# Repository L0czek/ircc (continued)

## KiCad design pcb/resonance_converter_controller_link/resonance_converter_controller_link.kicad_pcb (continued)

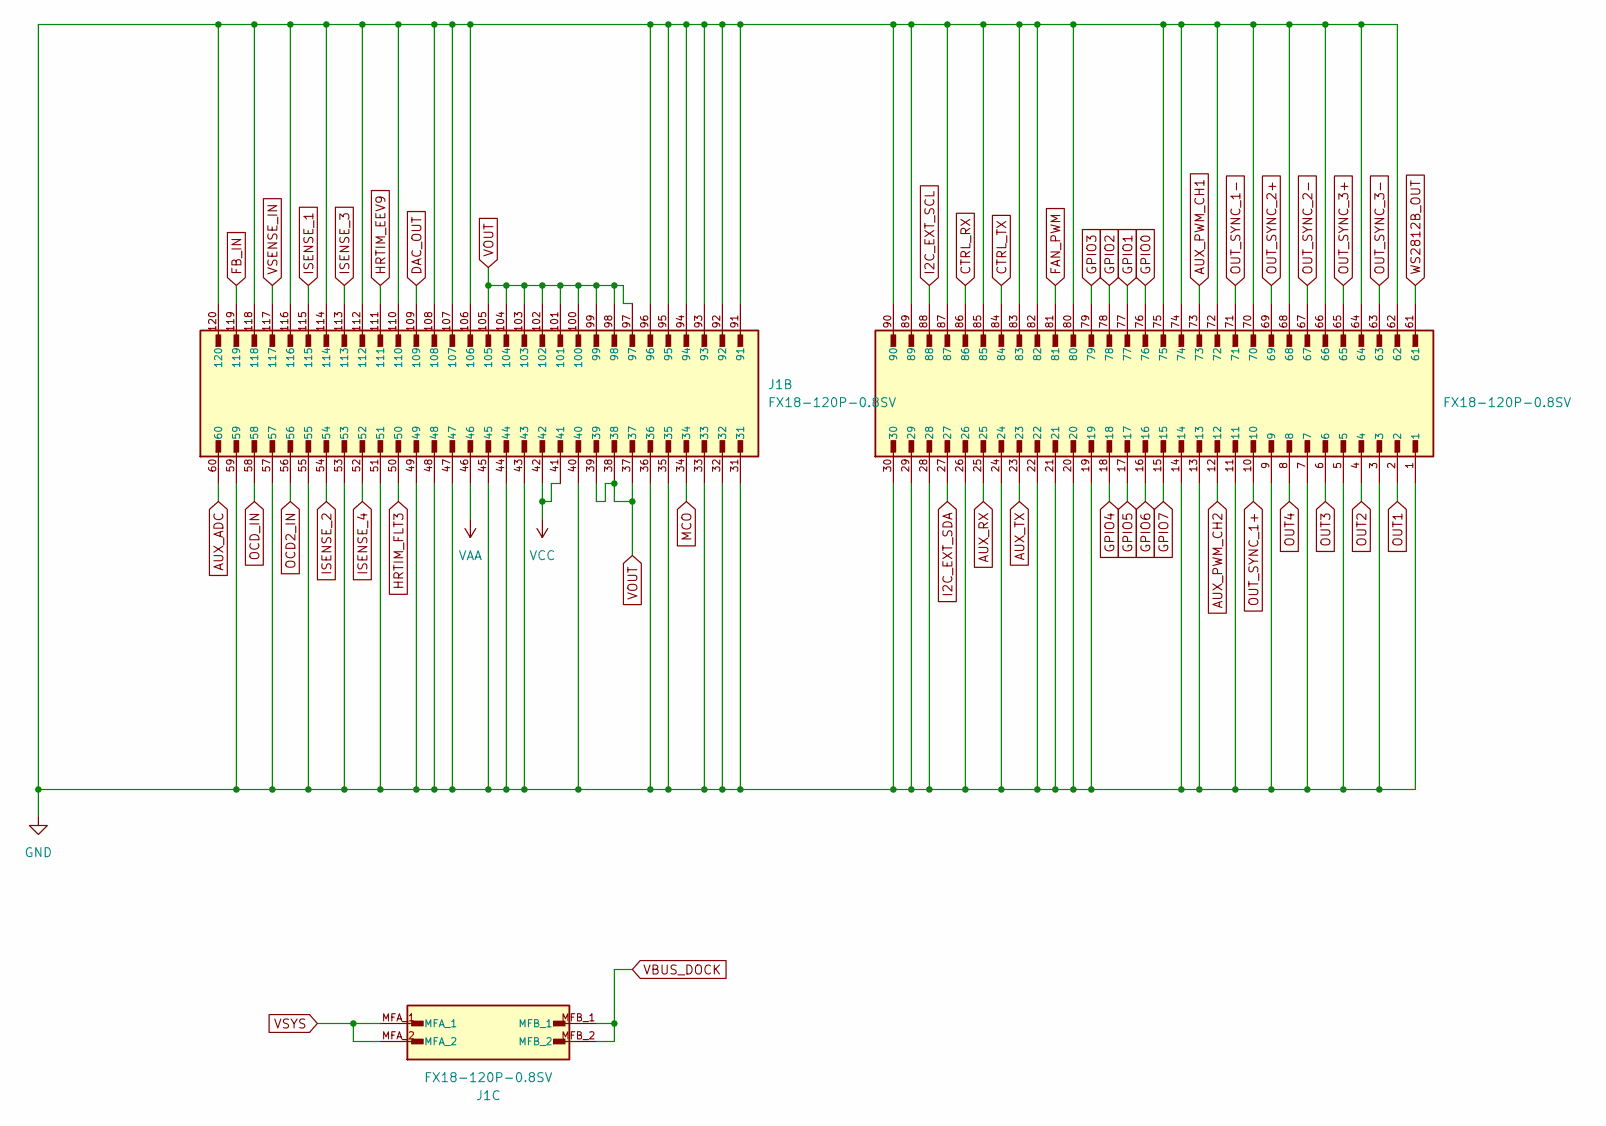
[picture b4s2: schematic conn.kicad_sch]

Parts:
J1: FX18-120P-0.8SV; HIROSE_FX18-120P-0.8SV; PARTREV 11.07.21

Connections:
AUX_ADC: J1.60; also elsewhere on the board
AUX_PWM_CH1: J1.73; also elsewhere on the board
AUX_PWM_CH2: J1.12; also elsewhere on the board
AUX_RX: J1.25; also elsewhere on the board
AUX_TX: J1.23; also elsewhere on the board
CTRL_RX: J1.86; also elsewhere on the board
CTRL_TX: J1.84; also elsewhere on the board
DAC_OUT: J1.109; also elsewhere on the board
FAN_PWM: J1.81; also elsewhere on the board
FB_IN: J1.119; also elsewhere on the board
GND: J1.1, J1.3, J1.5, J1.7, J1.9, J1.11, J1.13, J1.14, J1.19, J1.20, J1.21, J1.22, J1.24, J1.26, J1.28, J1.29, J1.30, J1.31, J1.32, J1.33, J1.35, J1.36, J1.40, J1.43, J1.44, J1.45, J1.47, J1.48, J1.49, J1.51, J1.53, J1.55, J1.57, J1.59, J1.62, J1.64, J1.66, J1.68, J1.70, J1.72, J1.74, J1.75, J1.80, J1.82, J1.83, J1.85, J1.87, J1.89, J1.90, J1.91, J1.92, J1.93, J1.94, J1.95, J1.96, J1.106, J1.107, J1.108, J1.110, J1.112, J1.114, J1.116, J1.118, J1.120; also elsewhere on the board
GPIO0: J1.76; also elsewhere on the board
GPIO1: J1.77; also elsewhere on the board
GPIO2: J1.78; also elsewhere on the board
GPIO3: J1.79; also elsewhere on the board
GPIO4: J1.18; also elsewhere on the board
GPIO5: J1.17; also elsewhere on the board
GPIO6: J1.16; also elsewhere on the board
GPIO7: J1.15; also elsewhere on the board
HRTIM_EEV9: J1.111; also elsewhere on the board
HRTIM_FLT3: J1.50; also elsewhere on the board
I2C_EXT_SCL: J1.88; also elsewhere on the board
I2C_EXT_SDA: J1.27; also elsewhere on the board
ISENSE_1: J1.115; also elsewhere on the board
ISENSE_2: J1.54; also elsewhere on the board
ISENSE_3: J1.113; also elsewhere on the board
ISENSE_4: J1.52; also elsewhere on the board
MCO: J1.34; also elsewhere on the board
OCD2_IN: J1.56; also elsewhere on the board
OCD_IN: J1.58; also elsewhere on the board
OUT1: J1.2; also elsewhere on the board
OUT2: J1.4; also elsewhere on the board
OUT3: J1.6; also elsewhere on the board
OUT4: J1.8; also elsewhere on the board
OUT_SYNC_1+: J1.10; also elsewhere on the board
OUT_SYNC_1-: J1.71; also elsewhere on the board
OUT_SYNC_2+: J1.69; also elsewhere on the board
OUT_SYNC_2-: J1.67; also elsewhere on the board
OUT_SYNC_3+: J1.65; also elsewhere on the board
OUT_SYNC_3-: J1.63; also elsewhere on the board
VAA: J1.46; also elsewhere on the board
VBUS_DOCK: J1.MFB_1, J1.MFB_2; also elsewhere on the board
VCC: J1.41, J1.42; also elsewhere on the board
VOUT: J1.37, J1.38, J1.39, J1.97, J1.98, J1.99, J1.100, J1.101, J1.102, J1.103, J1.104, J1.105; also elsewhere on the board
VSENSE_IN: J1.117; also elsewhere on the board
VSYS: J1.MFA_1, J1.MFA_2; also elsewhere on the board
WS2812B_OUT: J1.61; also elsewhere on the board

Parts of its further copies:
J2: FX18-120P-0.8SV; HIROSE_FX18-120P-0.8SV; PARTREV 11.07.21

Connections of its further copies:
AUX_ADC: J2.60; also elsewhere on the board
AUX_PWM_CH1: J2.73; also elsewhere on the board
AUX_PWM_CH2: J2.12; also elsewhere on the board
AUX_RX: J2.25; also elsewhere on the board
AUX_TX: J2.23; also elsewhere on the board
CTRL_RX: J2.86; also elsewhere on the board
CTRL_TX: J2.84; also elsewhere on the board
DAC_OUT: J2.109; also elsewhere on the board
FAN_PWM: J2.81; also elsewhere on the board
FB_IN: J2.119; also elsewhere on the board
GND: J2.1, J2.3, J2.5, J2.7, J2.9, J2.11, J2.13, J2.14, J2.19, J2.20, J2.21, J2.22, J2.24, J2.26, J2.28, J2.29, J2.30, J2.31, J2.32, J2.33, J2.35, J2.36, J2.40, J2.43, J2.44, J2.45, J2.47, J2.48, J2.49, J2.51, J2.53, J2.55, J2.57, J2.59, J2.62, J2.64, J2.66, J2.68, J2.70, J2.72, J2.74, J2.75, J2.80, J2.82, J2.83, J2.85, J2.87, J2.89, J2.90, J2.91, J2.92, J2.93, J2.94, J2.95, J2.96, J2.106, J2.107, J2.108, J2.110, J2.112, J2.114, J2.116, J2.118, J2.120; also elsewhere on the board
GPIO0: J2.76; also elsewhere on the board
GPIO1: J2.77; also elsewhere on the board
GPIO2: J2.78; also elsewhere on the board
GPIO3: J2.79; also elsewhere on the board
GPIO4: J2.18; also elsewhere on the board
GPIO5: J2.17; also elsewhere on the board
GPIO6: J2.16; also elsewhere on the board
GPIO7: J2.15; also elsewhere on the board
HRTIM_EEV9: J2.111; also elsewhere on the board
HRTIM_FLT3: J2.50; also elsewhere on the board
I2C_EXT_SCL: J2.88; also elsewhere on the board
I2C_EXT_SDA: J2.27; also elsewhere on the board
ISENSE_1: J2.115; also elsewhere on the board
ISENSE_2: J2.54; also elsewhere on the board
ISENSE_3: J2.113; also elsewhere on the board
ISENSE_4: J2.52; also elsewhere on the board
MCO: J2.34; also elsewhere on the board
OCD2_IN: J2.56; also elsewhere on the board
OCD_IN: J2.58; also elsewhere on the board
OUT1: J2.2; also elsewhere on the board
OUT2: J2.4; also elsewhere on the board
OUT3: J2.6; also elsewhere on the board
OUT4: J2.8; also elsewhere on the board
OUT_SYNC_1+: J2.10; also elsewhere on the board
OUT_SYNC_1-: J2.71; also elsewhere on the board
OUT_SYNC_2+: J2.69; also elsewhere on the board
OUT_SYNC_2-: J2.67; also elsewhere on the board
OUT_SYNC_3+: J2.65; also elsewhere on the board
OUT_SYNC_3-: J2.63; also elsewhere on the board
VAA: J2.46; also elsewhere on the board
VBUS_DOCK: J2.MFB_1, J2.MFB_2; also elsewhere on the board
VCC: J2.41, J2.42; also elsewhere on the board
VOUT: J2.37, J2.38, J2.39, J2.97, J2.98, J2.99, J2.100, J2.101, J2.102, J2.103, J2.104, J2.105; also elsewhere on the board
VSENSE_IN: J2.117; also elsewhere on the board
VSYS: J2.MFA_1, J2.MFA_2; also elsewhere on the board
WS2812B_OUT: J2.61; also elsewhere on the board

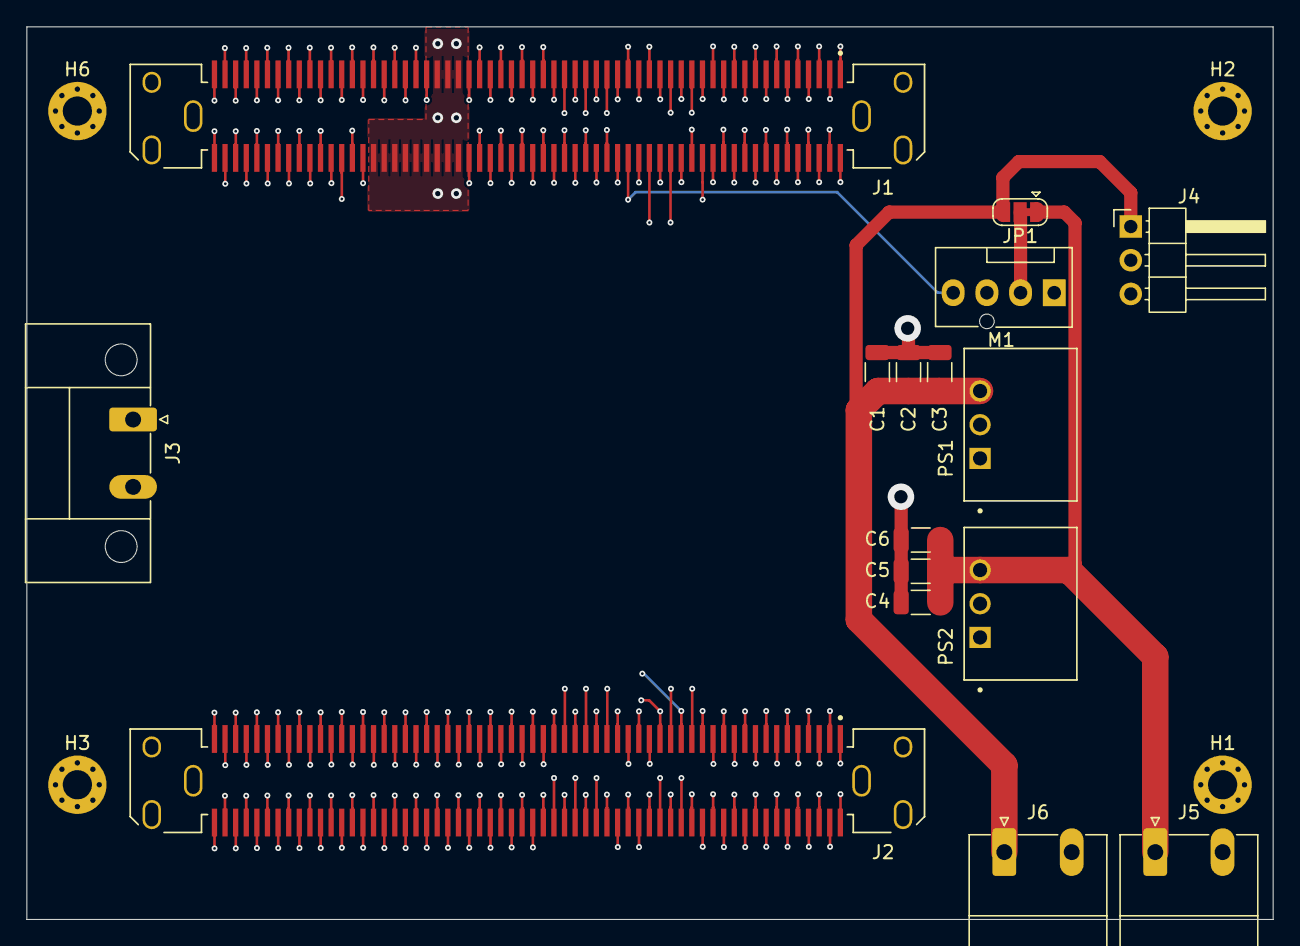
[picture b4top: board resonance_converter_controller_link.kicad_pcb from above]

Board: 6 copper layers, 94.0 x 67.3 mm, 20 parts (0 on the bottom side), 50 nets.

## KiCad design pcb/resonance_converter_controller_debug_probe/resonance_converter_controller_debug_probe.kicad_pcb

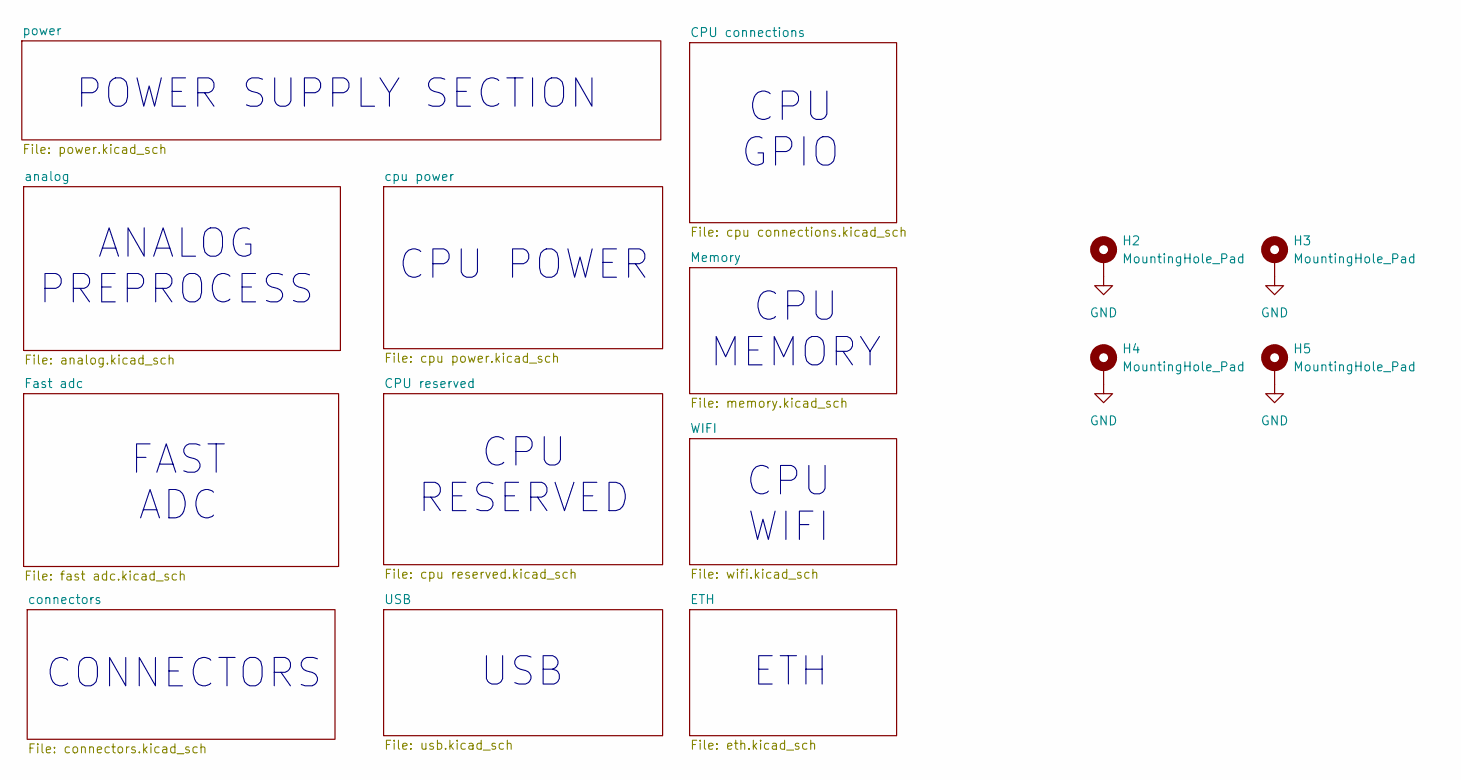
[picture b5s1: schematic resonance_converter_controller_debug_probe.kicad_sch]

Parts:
H2, H3, H4, H5: MountingHole_Pad; MountingHole_2.5mm_Pad_Via

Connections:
GND: H2.1 (1_1), H3.1 (1_1), H4.1 (1_1), H5.1 (1_1); also elsewhere on the board

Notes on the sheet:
CONNECTORS
CPU RESERVED
CPU GPIO
FAST ADC
ANALOG PREPROCESS
CPU MEMORY
USB
ETH
CPU POWER
CPU WIFI
POWER SUPPLY SECTION

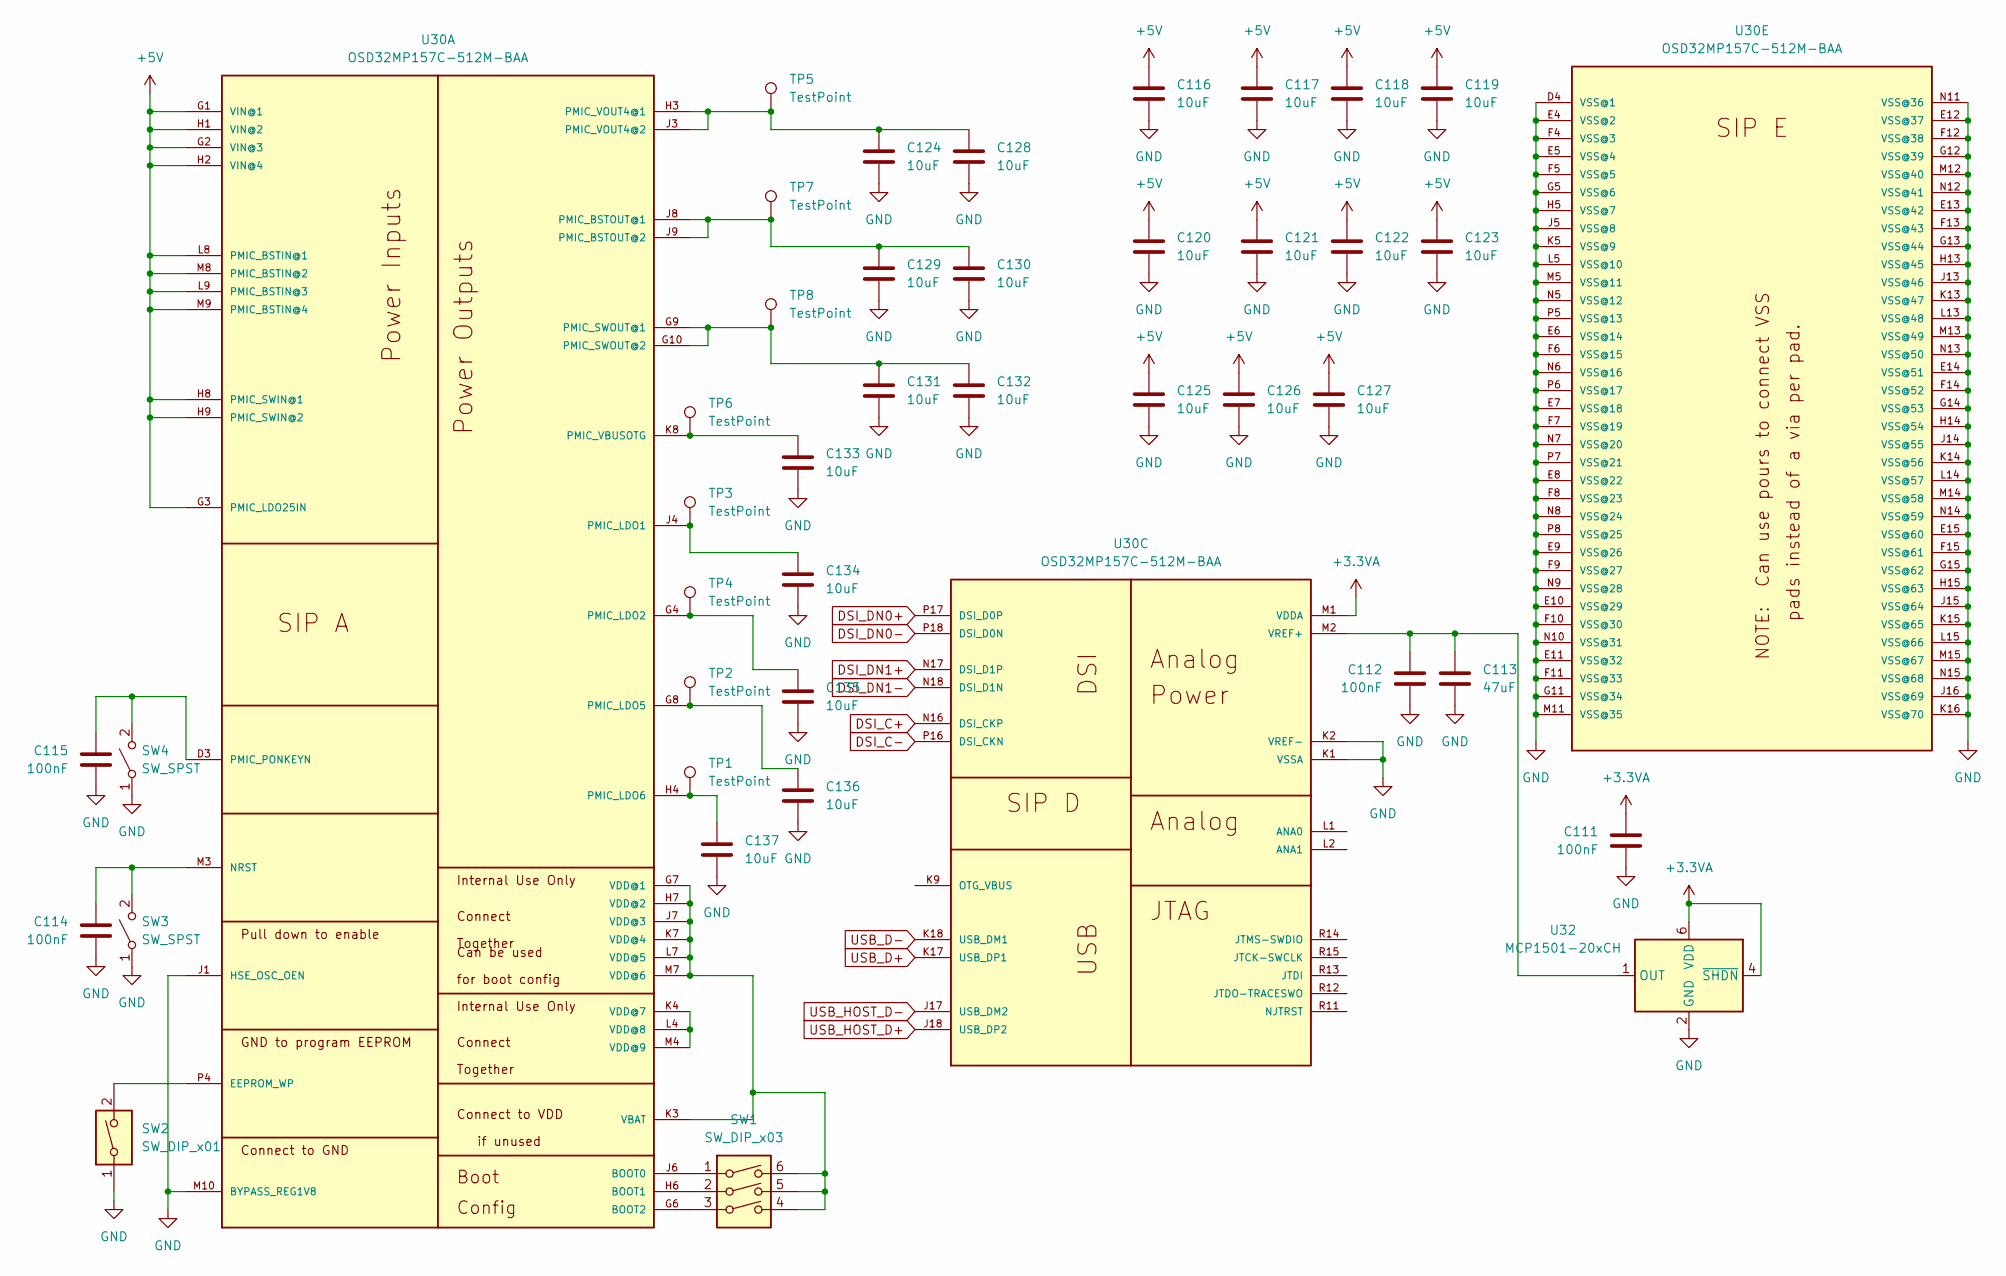
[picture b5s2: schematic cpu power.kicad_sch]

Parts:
C111, C112, C114, C115: 100nF; C_0402_1005Metric
C113: 47uF; C_1206_3216Metric
C116, C117, C118, C119, C120, C121, C122, C123, C124, C125, C126, C127, C128, C129, C130, C131, C132, C133, C134, C135, C136, C137: 10uF; C_0402_1005Metric
SW1: SW_DIP_x03; SW_DIP_SPSTx03_Slide_Omron_A6S-310x_W8.9mm_P2.54mm
SW2: SW_DIP_x01; SW_DIP_SPSTx01_Slide_Omron_A6S-110x_W8.9mm_P2.54mm
SW3, SW4: SW_SPST; SW_SPST_Omron_B3FS-100xP
TP1, TP2, TP3, TP4, TP5, TP6, TP7, TP8: TestPoint; TestPoint_Pad_D1.0mm
U30: OSD32MP157C-512M-BAA; OSD32MP15X-BGA-324
U32: MCP1501-20xCH; SOT-23-6

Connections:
+3.3VA: C111.1, U30.M1 (VDDA), U32.4 (~SHDN), U32.6 (VDD); also elsewhere on the board
+5V: C116.1, C117.1, C118.1, C119.1, C120.1, C121.1, C122.1, C123.1, C125.1, C126.1, C127.1, U30.G1 (VIN@1), U30.G2 (VIN@3), U30.G3 (PMIC_LDO25IN), U30.H1 (VIN@2), U30.H2 (VIN@4), U30.H8 (PMIC_SWIN@1), U30.H9 (PMIC_SWIN@2), U30.L8 (PMIC_BSTIN@1), U30.L9 (PMIC_BSTIN@3), U30.M8 (PMIC_BSTIN@2), U30.M9 (PMIC_BSTIN@4); also elsewhere on the board
DSI_C+: U30.N16 (DSI_CKP); also elsewhere on the board
DSI_C-: U30.P16 (DSI_CKN); also elsewhere on the board
DSI_DN0+: U30.P17 (DSI_D0P); also elsewhere on the board
DSI_DN0-: U30.P18 (DSI_D0N); also elsewhere on the board
DSI_DN1+: U30.N17 (DSI_D1P); also elsewhere on the board
DSI_DN1-: U30.N18 (DSI_D1N); also elsewhere on the board
GND: C111.2, C112.2, C113.2, C114.2, C115.2, C116.2, C117.2, C118.2, C119.2, C120.2, C121.2, C122.2, C123.2, C124.2, C125.2, C126.2, C127.2, C128.2, C129.2, C130.2, C131.2, C132.2, C133.2, C134.2, C135.2, C136.2, C137.2, SW2.1, SW3.1 (A), SW4.1 (A), U30.D4 (VSS@1), U30.E4 (VSS@2), U30.E5 (VSS@4), U30.E6 (VSS@14), U30.E7 (VSS@18), U30.E8 (VSS@22), U30.E9 (VSS@26), U30.E10 (VSS@29), U30.E11 (VSS@32), U30.E12 (VSS@37), U30.E13 (VSS@42), U30.E14 (VSS@51), U30.E15 (VSS@60), U30.F4 (VSS@3), U30.F5 (VSS@5), U30.F6 (VSS@15), U30.F7 (VSS@19), U30.F8 (VSS@23), U30.F9 (VSS@27), U30.F10 (VSS@30), U30.F11 (VSS@33), U30.F12 (VSS@38), U30.F13 (VSS@43), U30.F14 (VSS@52), U30.F15 (VSS@61), U30.G5 (VSS@6), U30.G11 (VSS@34), U30.G12 (VSS@39), U30.G13 (VSS@44), U30.G14 (VSS@53), U30.G15 (VSS@62), U30.H5 (VSS@7), U30.H13 (VSS@45), U30.H14 (VSS@54), U30.H15 (VSS@63), U30.J1 (HSE_OSC_OEN), U30.J5 (VSS@8), U30.J13 (VSS@46), U30.J14 (VSS@55), U30.J15 (VSS@64), U30.J16 (VSS@69), U30.K1 (VSSA), U30.K2 (VREF-), U30.K5 (VSS@9), U30.K13 (VSS@47), U30.K14 (VSS@56), U30.K15 (VSS@65), U30.K16 (VSS@70), U30.L5 (VSS@10), U30.L13 (VSS@48), U30.L14 (VSS@57), U30.L15 (VSS@66), U30.M5 (VSS@11), U30.M10 (BYPASS_REG1V8), U30.M11 (VSS@35), U30.M12 (VSS@40), U30.M13 (VSS@49), U30.M14 (VSS@58), U30.M15 (VSS@67), U30.N5 (VSS@12), U30.N6 (VSS@16), U30.N7 (VSS@20), U30.N8 (VSS@24), U30.N9 (VSS@28), U30.N10 (VSS@31), U30.N11 (VSS@36), U30.N12 (VSS@41), U30.N13 (VSS@50), U30.N14 (VSS@59), U30.N15 (VSS@68), U30.P5 (VSS@13), U30.P6 (VSS@17), U30.P7 (VSS@21), U30.P8 (VSS@25), U32.2 (GND), U32.3 (GND), U32.5 (GND); also elsewhere on the board
unnamed: C114.1, SW3.2 (B), U30.M3 (NRST)
unnamed: C115.1, SW4.2 (B), U30.D3 (PMIC_PONKEYN)
unnamed: SW1.1, U30.J6 (BOOT0)
unnamed: SW1.2, U30.H6 (BOOT1)
unnamed: SW1.3, U30.G6 (BOOT2)
unnamed: SW2.2, U30.P4 (EEPROM_WP)
unnamed: C129.1, C130.1, TP7.1, U30.J8 (PMIC_BSTOUT@1), U30.J9 (PMIC_BSTOUT@2)
unnamed: C134.1, TP3.1, U30.J4 (PMIC_LDO1)
unnamed: C135.1, TP4.1, U30.G4 (PMIC_LDO2)
unnamed: C136.1, TP2.1, U30.G8 (PMIC_LDO5)
unnamed: C137.1, TP1.1, U30.H4 (PMIC_LDO6)
unnamed: C131.1, C132.1, TP8.1, U30.G9 (PMIC_SWOUT@1), U30.G10 (PMIC_SWOUT@2)
unnamed: C133.1, TP6.1, U30.K8 (PMIC_VBUSOTG)
unnamed: C124.1, C128.1, TP5.1, U30.H3 (PMIC_VOUT4@1), U30.J3 (PMIC_VOUT4@2)
unnamed: SW1.4, SW1.5, SW1.6, U30.G7 (VDD@1), U30.H7 (VDD@2), U30.J7 (VDD@3), U30.K3 (VBAT), U30.K7 (VDD@4), U30.L7 (VDD@5), U30.M7 (VDD@6)
unnamed: U30.K4 (VDD@7), U30.L4 (VDD@8), U30.M4 (VDD@9)
unnamed: C112.1, C113.1, U30.M2 (VREF+), U32.1 (OUT)
USB_D+: U30.K17 (USB_DP1); also elsewhere on the board
USB_D-: U30.K18 (USB_DM1); also elsewhere on the board
USB_HOST_D+: U30.J18 (USB_DP2); also elsewhere on the board
USB_HOST_D-: U30.J17 (USB_DM2); also elsewhere on the board

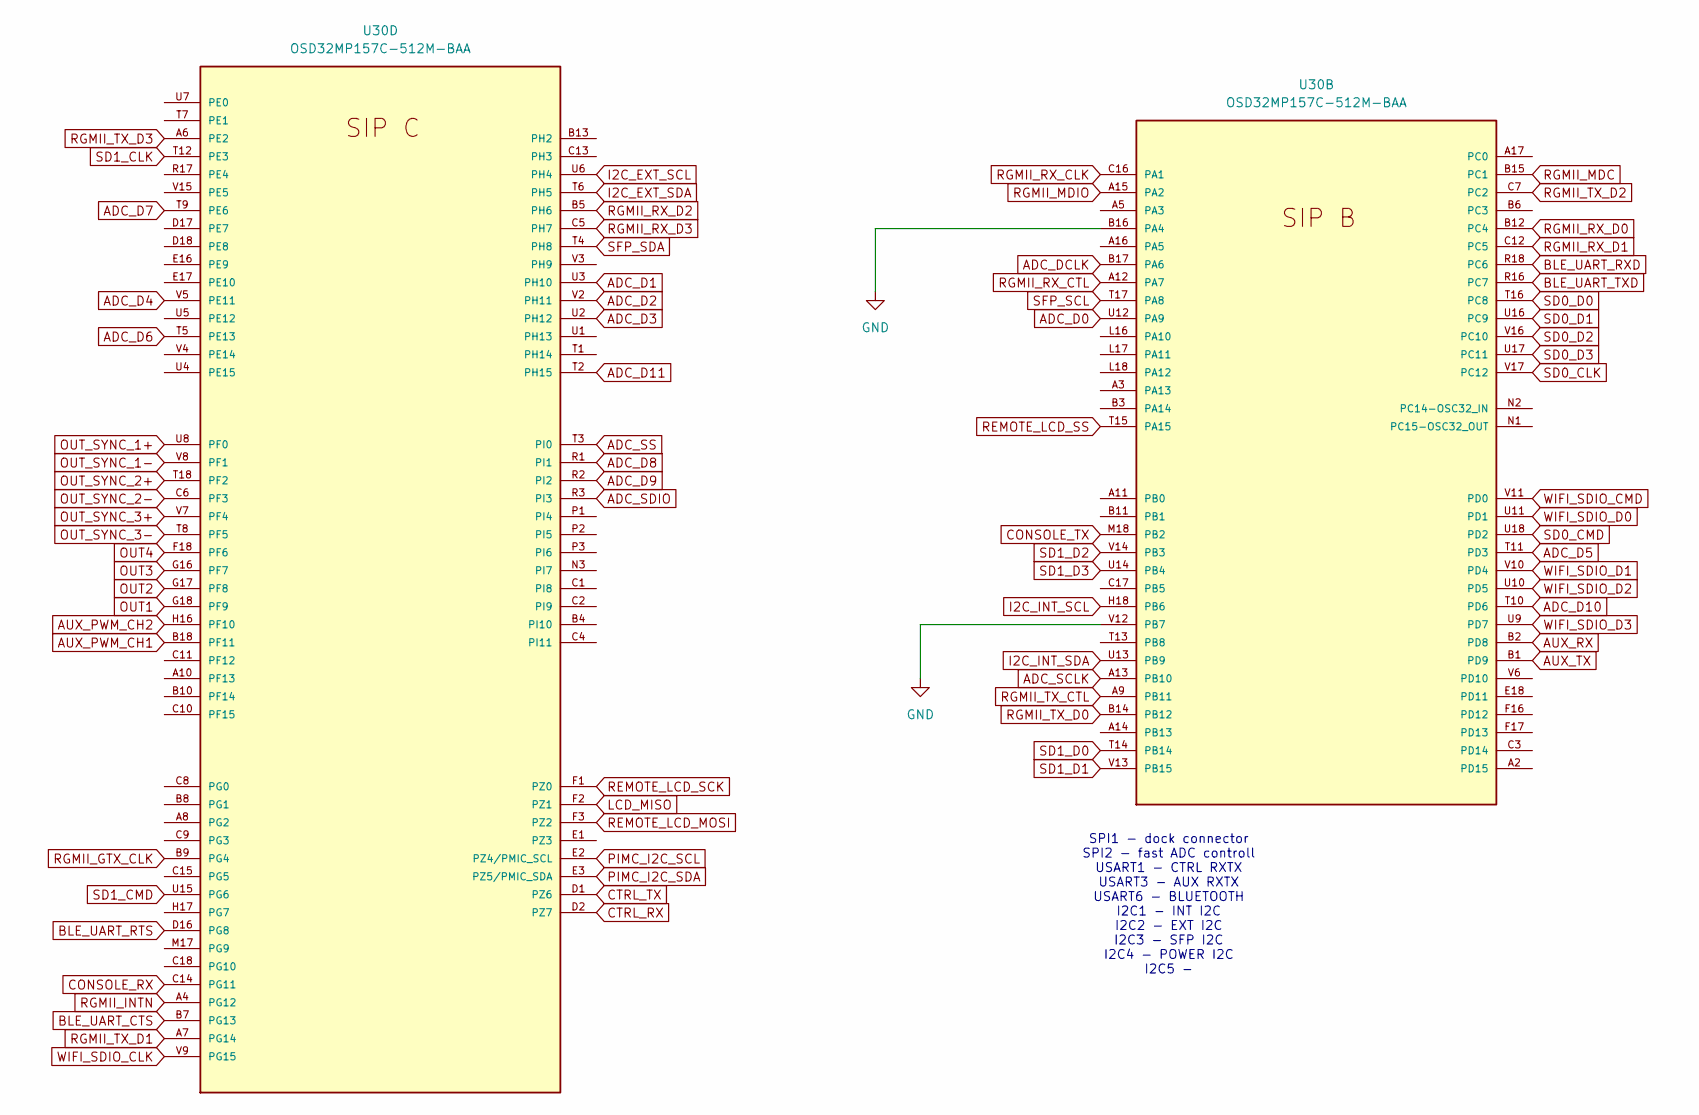
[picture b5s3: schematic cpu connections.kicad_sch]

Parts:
U30: OSD32MP157C-512M-BAA; OSD32MP15X-BGA-324

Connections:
ADC_D0: U30.U12 (PA9); also elsewhere on the board
ADC_D1: U30.U3 (PH10); also elsewhere on the board
ADC_D2: U30.V2 (PH11); also elsewhere on the board
ADC_D3: U30.U2 (PH12); also elsewhere on the board
ADC_D4: U30.V5 (PE11); also elsewhere on the board
ADC_D5: U30.T11 (PD3); also elsewhere on the board
ADC_D6: U30.T5 (PE13); also elsewhere on the board
ADC_D7: U30.T9 (PE6); also elsewhere on the board
ADC_D8: U30.R1 (PI1); also elsewhere on the board
ADC_D9: U30.R2 (PI2); also elsewhere on the board
ADC_D10: U30.T10 (PD6); also elsewhere on the board
ADC_D11: U30.T2 (PH15); also elsewhere on the board
ADC_DCLK: U30.B17 (PA6); also elsewhere on the board
ADC_SCLK: U30.A13 (PB10); also elsewhere on the board
ADC_SDIO: U30.R3 (PI3); also elsewhere on the board
ADC_SS: U30.T3 (PI0); also elsewhere on the board
AUX_PWM_CH1: U30.B18 (PF11); also elsewhere on the board
AUX_PWM_CH2: U30.H16 (PF10); also elsewhere on the board
AUX_RX: U30.B2 (PD8); also elsewhere on the board
AUX_TX: U30.B1 (PD9); also elsewhere on the board
BLE_UART_CTS: U30.B7 (PG13); also elsewhere on the board
BLE_UART_RTS: U30.D16 (PG8); also elsewhere on the board
BLE_UART_RXD: U30.R18 (PC6); also elsewhere on the board
BLE_UART_TXD: U30.R16 (PC7); also elsewhere on the board
CONSOLE_RX: U30.C14 (PG11); also elsewhere on the board
CONSOLE_TX: U30.M18 (PB2); also elsewhere on the board
CTRL_RX: U30.D2 (PZ7); also elsewhere on the board
CTRL_TX: U30.D1 (PZ6); also elsewhere on the board
GND: U30.B16 (PA4), U30.V12 (PB7); also elsewhere on the board
I2C_EXT_SCL: U30.U6 (PH4); also elsewhere on the board
I2C_EXT_SDA: U30.T6 (PH5); also elsewhere on the board
I2C_INT_SCL: U30.H18 (PB6); also elsewhere on the board
I2C_INT_SDA: U30.U13 (PB9); also elsewhere on the board
LCD_MISO: U30.F2 (PZ1)
OUT1: U30.G18 (PF9); also elsewhere on the board
OUT2: U30.G17 (PF8); also elsewhere on the board
OUT3: U30.G16 (PF7); also elsewhere on the board
OUT4: U30.F18 (PF6); also elsewhere on the board
OUT_SYNC_1+: U30.U8 (PF0); also elsewhere on the board
OUT_SYNC_1-: U30.V8 (PF1); also elsewhere on the board
OUT_SYNC_2+: U30.T18 (PF2); also elsewhere on the board
OUT_SYNC_2-: U30.C6 (PF3); also elsewhere on the board
OUT_SYNC_3+: U30.V7 (PF4); also elsewhere on the board
OUT_SYNC_3-: U30.T8 (PF5); also elsewhere on the board
PIMC_I2C_SCL: U30.E2 (PZ4/PMIC_SCL)
PIMC_I2C_SDA: U30.E3 (PZ5/PMIC_SDA)
REMOTE_LCD_MOSI: U30.F3 (PZ2)
REMOTE_LCD_SCK: U30.F1 (PZ0)
REMOTE_LCD_SS: U30.T15 (PA15)
RGMII_GTX_CLK: U30.B9 (PG4); also elsewhere on the board
RGMII_INTN: U30.A4 (PG12); also elsewhere on the board
RGMII_MDC: U30.B15 (PC1); also elsewhere on the board
RGMII_MDIO: U30.A15 (PA2); also elsewhere on the board
RGMII_RX_CLK: U30.C16 (PA1); also elsewhere on the board
RGMII_RX_CTL: U30.A12 (PA7); also elsewhere on the board
RGMII_RX_D0: U30.B12 (PC4); also elsewhere on the board
RGMII_RX_D1: U30.C12 (PC5); also elsewhere on the board
RGMII_RX_D2: U30.B5 (PH6); also elsewhere on the board
RGMII_RX_D3: U30.C5 (PH7); also elsewhere on the board
RGMII_TX_CTL: U30.A9 (PB11); also elsewhere on the board
RGMII_TX_D0: U30.B14 (PB12); also elsewhere on the board
RGMII_TX_D1: U30.A7 (PG14); also elsewhere on the board
RGMII_TX_D2: U30.C7 (PC2); also elsewhere on the board
RGMII_TX_D3: U30.A6 (PE2); also elsewhere on the board
SD0_CLK: U30.V17 (PC12); also elsewhere on the board
SD0_CMD: U30.U18 (PD2); also elsewhere on the board
SD0_D0: U30.T16 (PC8); also elsewhere on the board
SD0_D1: U30.U16 (PC9); also elsewhere on the board
SD0_D2: U30.V16 (PC10); also elsewhere on the board
SD0_D3: U30.U17 (PC11); also elsewhere on the board
SD1_CLK: U30.T12 (PE3); also elsewhere on the board
SD1_CMD: U30.U15 (PG6); also elsewhere on the board
SD1_D0: U30.T14 (PB14); also elsewhere on the board
SD1_D1: U30.V13 (PB15); also elsewhere on the board
SD1_D2: U30.V14 (PB3); also elsewhere on the board
SD1_D3: U30.U14 (PB4); also elsewhere on the board
SFP_SCL: U30.T17 (PA8); also elsewhere on the board
SFP_SDA: U30.T4 (PH8); also elsewhere on the board
WIFI_SDIO_CLK: U30.V9 (PG15); also elsewhere on the board
WIFI_SDIO_CMD: U30.V11 (PD0); also elsewhere on the board
WIFI_SDIO_D0: U30.U11 (PD1); also elsewhere on the board
WIFI_SDIO_D1: U30.V10 (PD4); also elsewhere on the board
WIFI_SDIO_D2: U30.U10 (PD5); also elsewhere on the board
WIFI_SDIO_D3: U30.U9 (PD7); also elsewhere on the board

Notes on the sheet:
SPI1 - dock connector SPI2 - fast ADC controll USART1 - CTRL RXTX USART3 - AUX RXTX USART6 - BLUETOOTH I2C1 - INT I2C I2C2 - EXT I2C I2C3 - SFP I2C I2C4 - POWER I2C I2C5 -

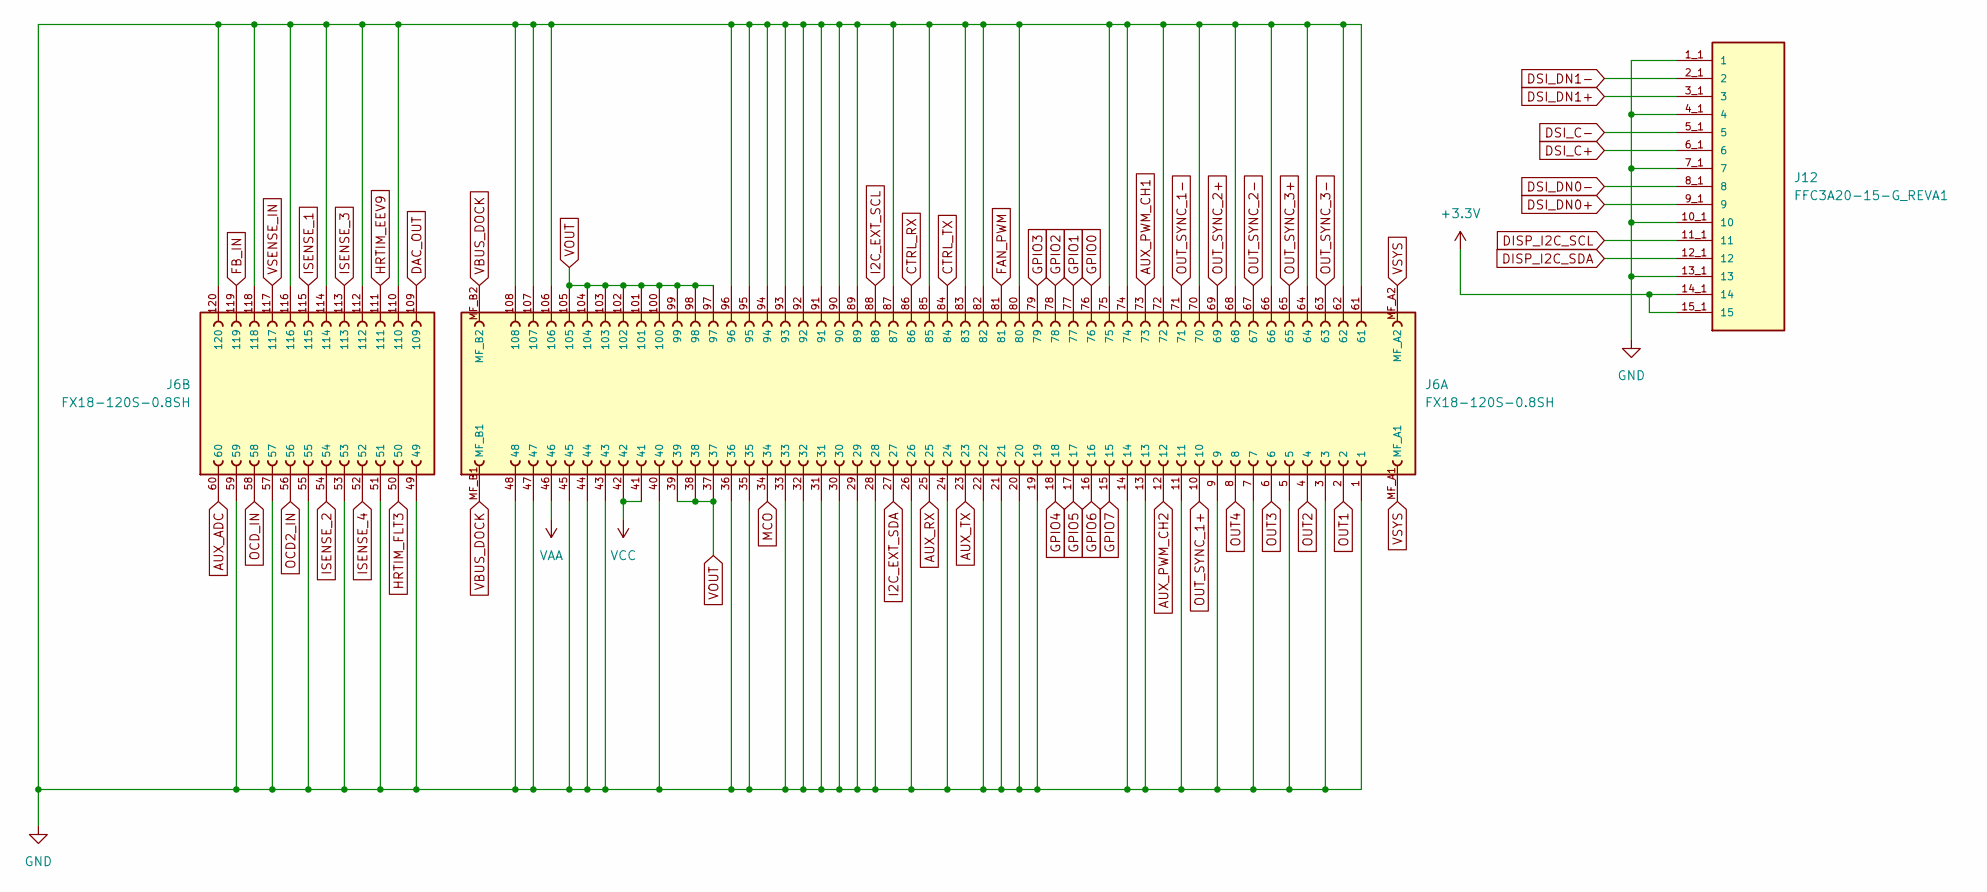
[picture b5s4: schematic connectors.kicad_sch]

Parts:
J6: FX18-120S-0.8SH; HIROSE_FX18-120S-0.8SH; PARTREV 1
J12: FFC3A20-15-G_REVA1; GCT_FFC3A20-15-G_REVA1; PARTREV A1

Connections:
+3.3V: J12.14_1 (14), J12.14_2 (14), J12.15_1 (15), J12.15_2 (15); also elsewhere on the board
AUX_ADC: J6.60; also elsewhere on the board
AUX_PWM_CH1: J6.73; also elsewhere on the board
AUX_PWM_CH2: J6.12; also elsewhere on the board
AUX_RX: J6.25; also elsewhere on the board
AUX_TX: J6.23; also elsewhere on the board
CTRL_RX: J6.86; also elsewhere on the board
CTRL_TX: J6.84; also elsewhere on the board
DAC_OUT: J6.109; also elsewhere on the board
DISP_I2C_SCL: J12.11_1 (11), J12.11_2 (11)
DISP_I2C_SDA: J12.12_1 (12), J12.12_2 (12)
DSI_C+: J12.6_1 (6), J12.6_2 (6); also elsewhere on the board
DSI_C-: J12.5_1 (5), J12.5_2 (5); also elsewhere on the board
DSI_DN0+: J12.9_1 (9), J12.9_2 (9); also elsewhere on the board
DSI_DN0-: J12.8_1 (8), J12.8_2 (8); also elsewhere on the board
DSI_DN1+: J12.3_1 (3), J12.3_2 (3); also elsewhere on the board
DSI_DN1-: J12.2_1 (2), J12.2_2 (2); also elsewhere on the board
FAN_PWM: J6.81
FB_IN: J6.119
GND: J6.1, J6.3, J6.5, J6.7, J6.9, J6.11, J6.13, J6.14, J6.19, J6.20, J6.21, J6.22, J6.24, J6.26, J6.28, J6.29, J6.30, J6.31, J6.32, J6.33, J6.35, J6.36, J6.40, J6.43, J6.44, J6.45, J6.47, J6.48, J6.49, J6.51, J6.53, J6.55, J6.57, J6.59, J6.61, J6.62, J6.64, J6.66, J6.68, J6.70, J6.72, J6.74, J6.75, J6.80, J6.82, J6.83, J6.85, J6.87, J6.89, J6.90, J6.91, J6.92, J6.93, J6.94, J6.95, J6.96, J6.106, J6.107, J6.108, J6.110, J6.112, J6.114, J6.116, J6.118, J6.120, J12.1_1 (1), J12.1_2 (1), J12.4_1 (4), J12.4_2 (4), J12.7_1 (7), J12.7_2 (7), J12.10_1 (10), J12.10_2 (10), J12.13_1 (13), J12.13_2 (13); also elsewhere on the board
GPIO0: J6.76
GPIO1: J6.77
GPIO2: J6.78
GPIO3: J6.79
GPIO4: J6.18
GPIO5: J6.17
GPIO6: J6.16
GPIO7: J6.15
HRTIM_EEV9: J6.111
HRTIM_FLT3: J6.50
I2C_EXT_SCL: J6.88; also elsewhere on the board
I2C_EXT_SDA: J6.27; also elsewhere on the board
ISENSE_1: J6.115; also elsewhere on the board
ISENSE_2: J6.54; also elsewhere on the board
ISENSE_3: J6.113; also elsewhere on the board
ISENSE_4: J6.52; also elsewhere on the board
MCO: J6.34
OCD2_IN: J6.56; also elsewhere on the board
OCD_IN: J6.58; also elsewhere on the board
OUT1: J6.2; also elsewhere on the board
OUT2: J6.4; also elsewhere on the board
OUT3: J6.6; also elsewhere on the board
OUT4: J6.8; also elsewhere on the board
OUT_SYNC_1+: J6.10; also elsewhere on the board
OUT_SYNC_1-: J6.71; also elsewhere on the board
OUT_SYNC_2+: J6.69; also elsewhere on the board
OUT_SYNC_2-: J6.67; also elsewhere on the board
OUT_SYNC_3+: J6.65; also elsewhere on the board
OUT_SYNC_3-: J6.63; also elsewhere on the board
VAA: J6.46
VBUS_DOCK: J6.MF_B1, J6.MF_B2; also elsewhere on the board
VCC: J6.41, J6.42
VOUT: J6.37, J6.38, J6.39, J6.97, J6.98, J6.99, J6.100, J6.101, J6.102, J6.103, J6.104, J6.105
VSENSE_IN: J6.117; also elsewhere on the board
VSYS: J6.MF_A1, J6.MF_A2; also elsewhere on the board
